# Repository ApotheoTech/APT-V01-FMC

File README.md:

# APT-V01-FMC
CopyRight 2023 ApotheoTech 

## Description

The GPIO board is made mostly for enabling GPIO access to any FMC card connector. It has a Raspberry Pi hat compliant connector, and two PMODs that can be used by PMODs that require two adjacent connectors. 

It also has an M.2 Key E connector with a ULPI USB 2.0 interface and 1 PCIe TX and RX connection to support Wifi and Bluetooth. 

## Example Designs 

Navigate up to the repository under example designs (TBD link). 

## Projected Use Cases

Mostly Debugging and providing Wifi accesses to PetaLinux builds

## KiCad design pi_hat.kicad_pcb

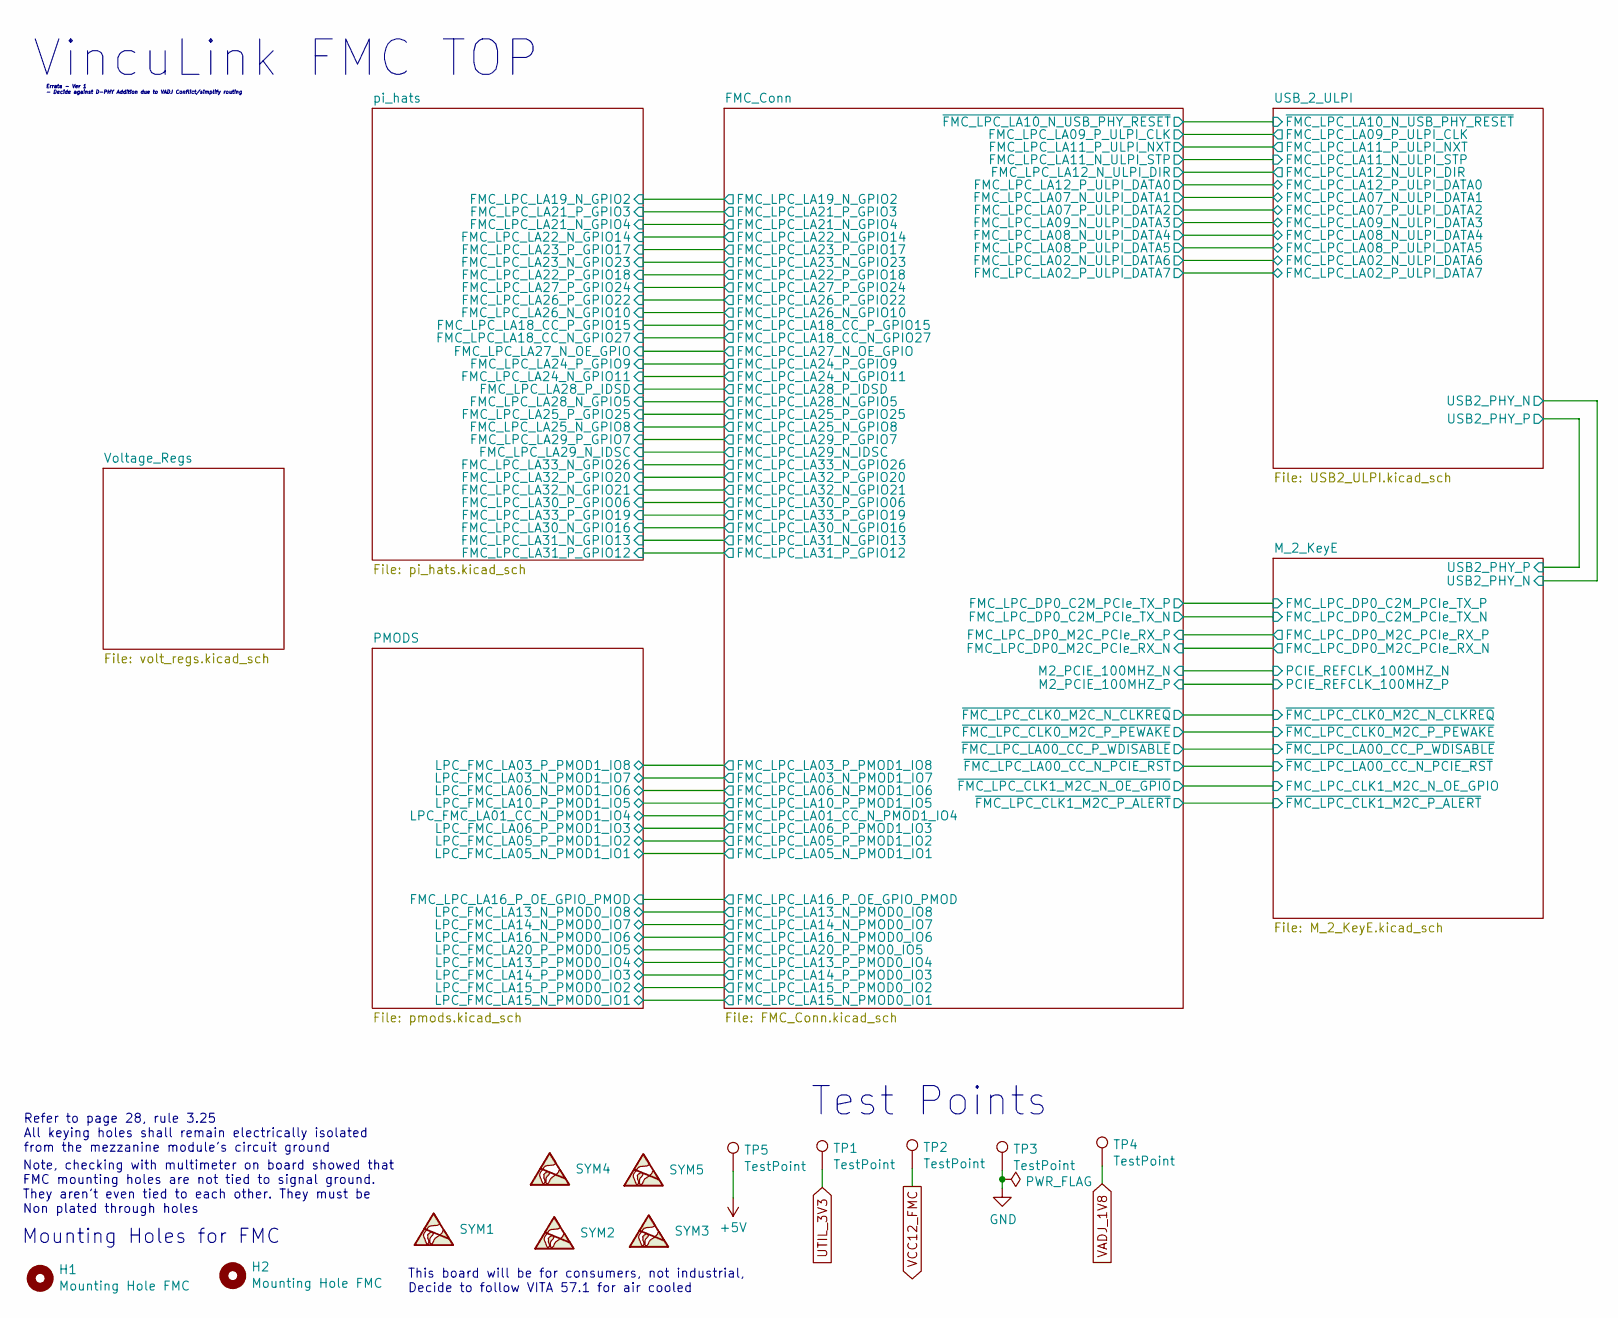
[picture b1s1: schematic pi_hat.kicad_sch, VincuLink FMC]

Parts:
H1, H2: Mounting Hole FMC; MountingHole_2.7mm_M2.5_Pad_2.9mm
SYM1: SYM_ESD_Small; ApotheoTech_Sym
SYM2: SYM_ESD_Small; WEEE-Logo_4.2x6mm_SilkScreen
SYM3: SYM_ESD_Small; ESD-Logo_6.6x6mm_SilkScreen
SYM4: SYM_ESD_Small; CE-Logo_8.5x6mm_SilkScreen
SYM5: SYM_ESD_Small; UKCA_Logo_8_5mm
TP1, TP2, TP3, TP4, TP5: TestPoint

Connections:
+5V: TP5.1; also elsewhere on the board
GND: TP3.1; also elsewhere on the board
UTIL_3V3: TP1.1; also elsewhere on the board
VADJ_1V8: TP4.1; also elsewhere on the board
VCC12_FMC: TP2.1; also elsewhere on the board

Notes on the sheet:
Refer to page 28, rule 3.25 All keying holes shall remain electrically isolated from the mezzanine module's circuit ground
Mounting Holes for FMC
Test Points
Note, checking with multimeter on board showed that FMC mounting holes are not tied to signal ground. They aren't even tied to each other. They must be Non plated through holes
Errata - Ver 1 - Decide against D-PHY Addition due to VADJ Conflict/simplify routing
VincuLink FMC TOP
This board will be for consumers, not industrial, Decide to follow VITA 57.1 for air cooled

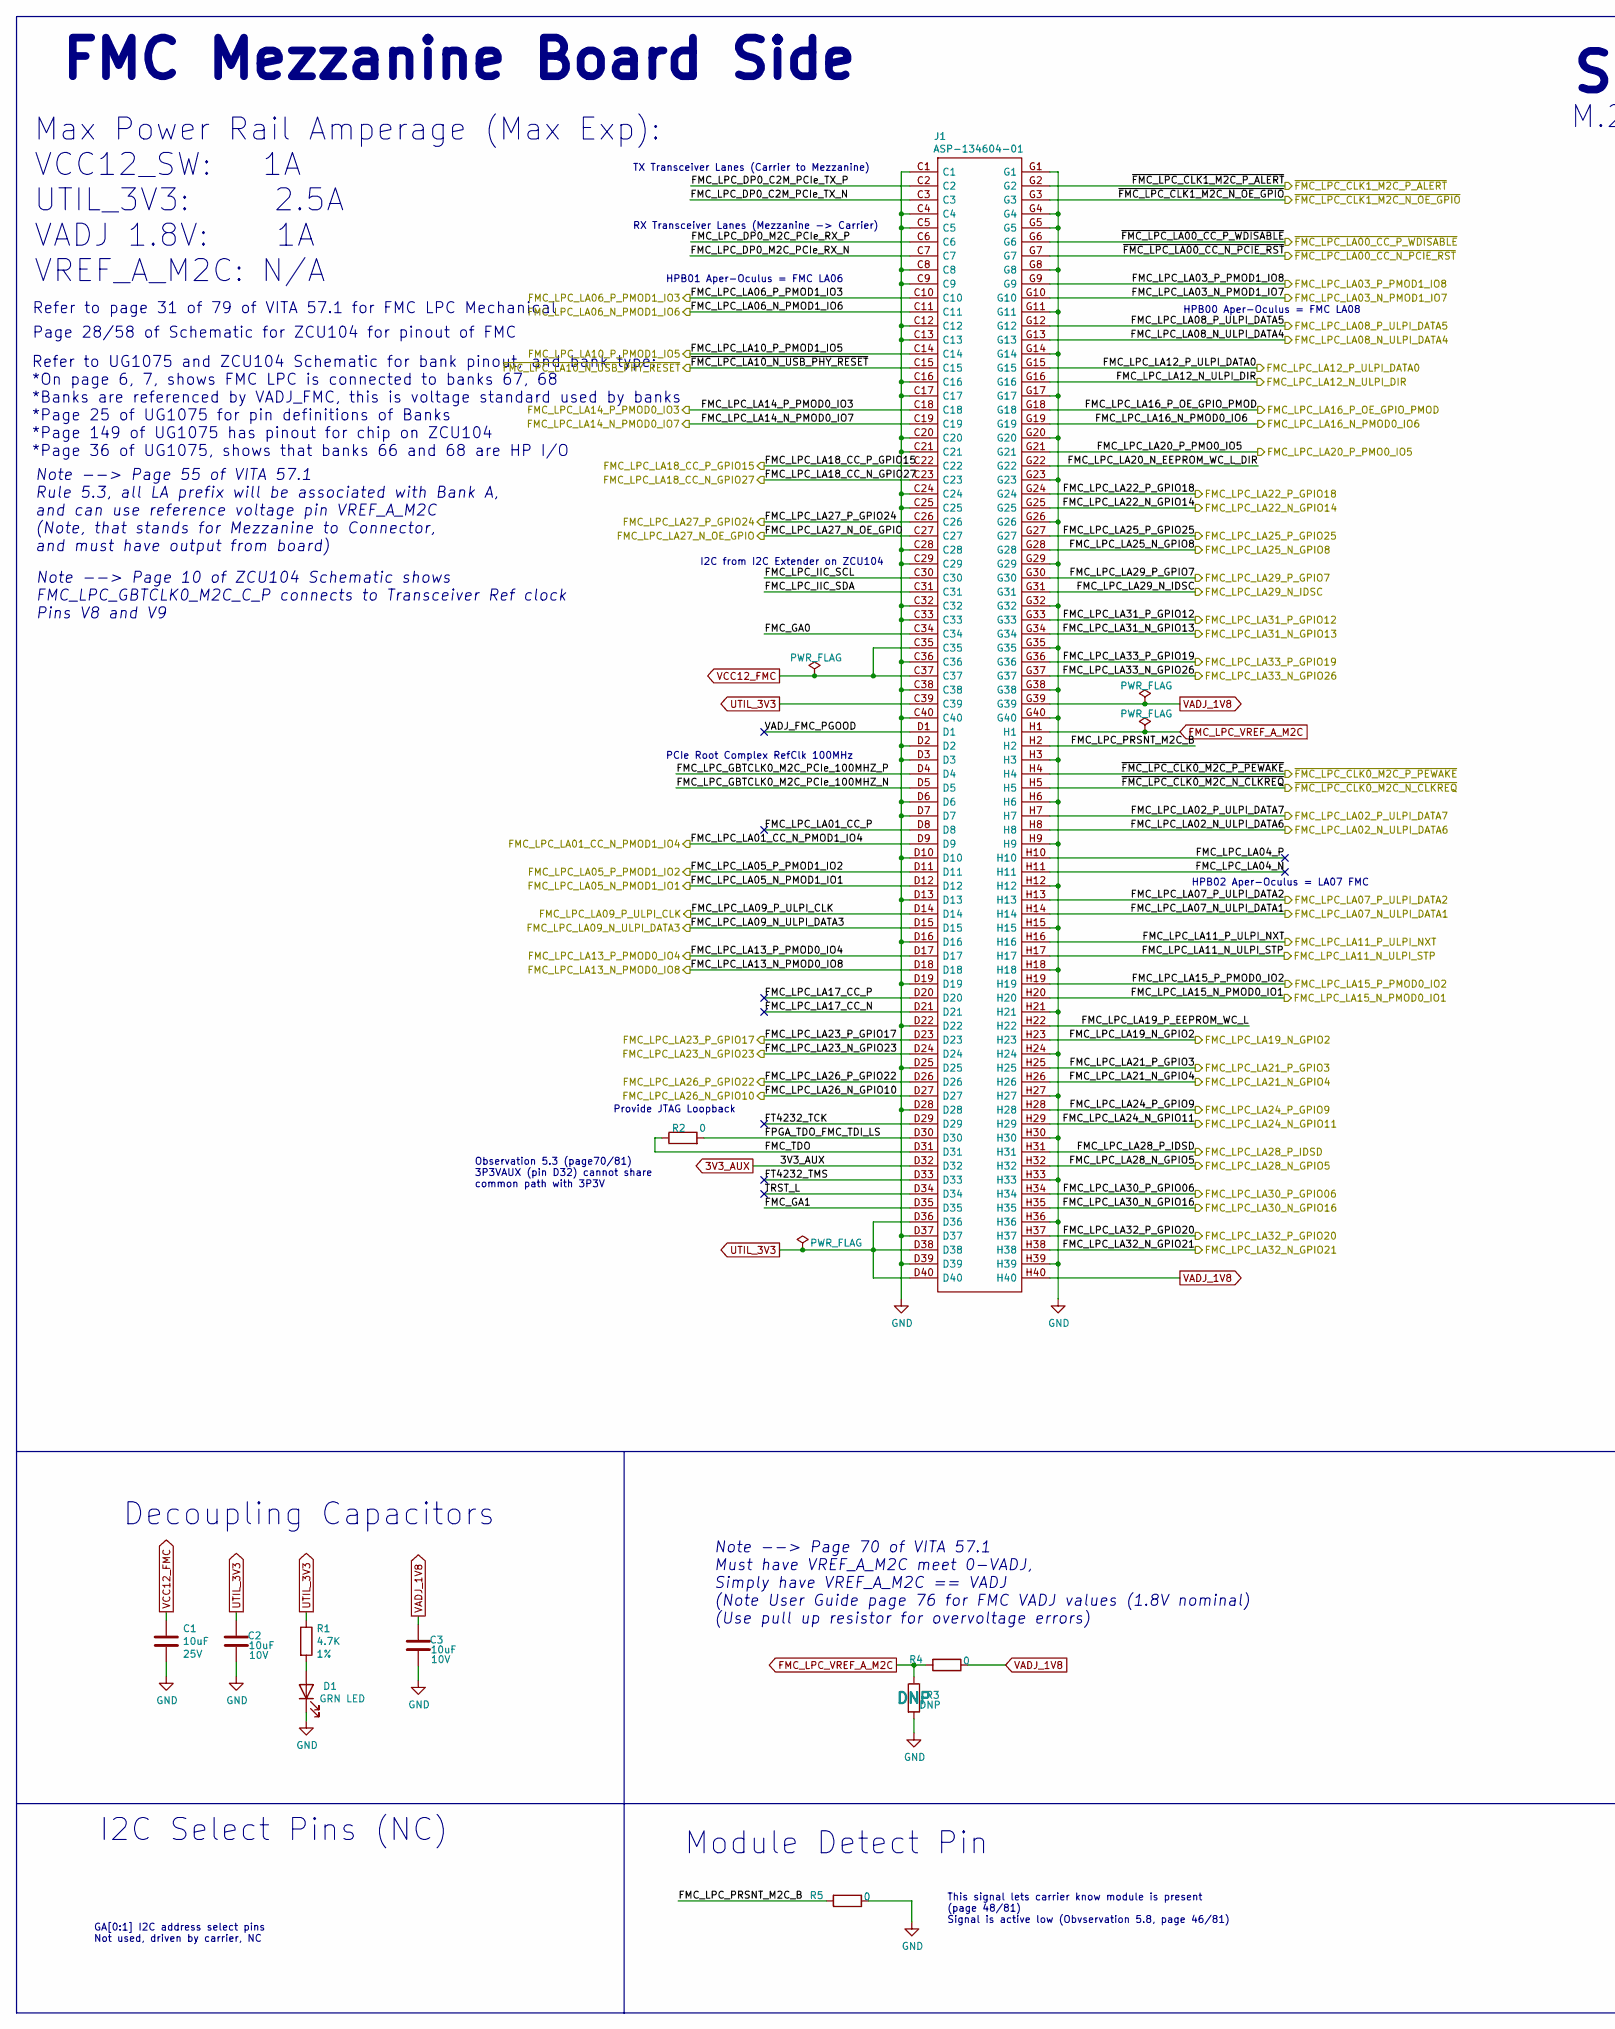
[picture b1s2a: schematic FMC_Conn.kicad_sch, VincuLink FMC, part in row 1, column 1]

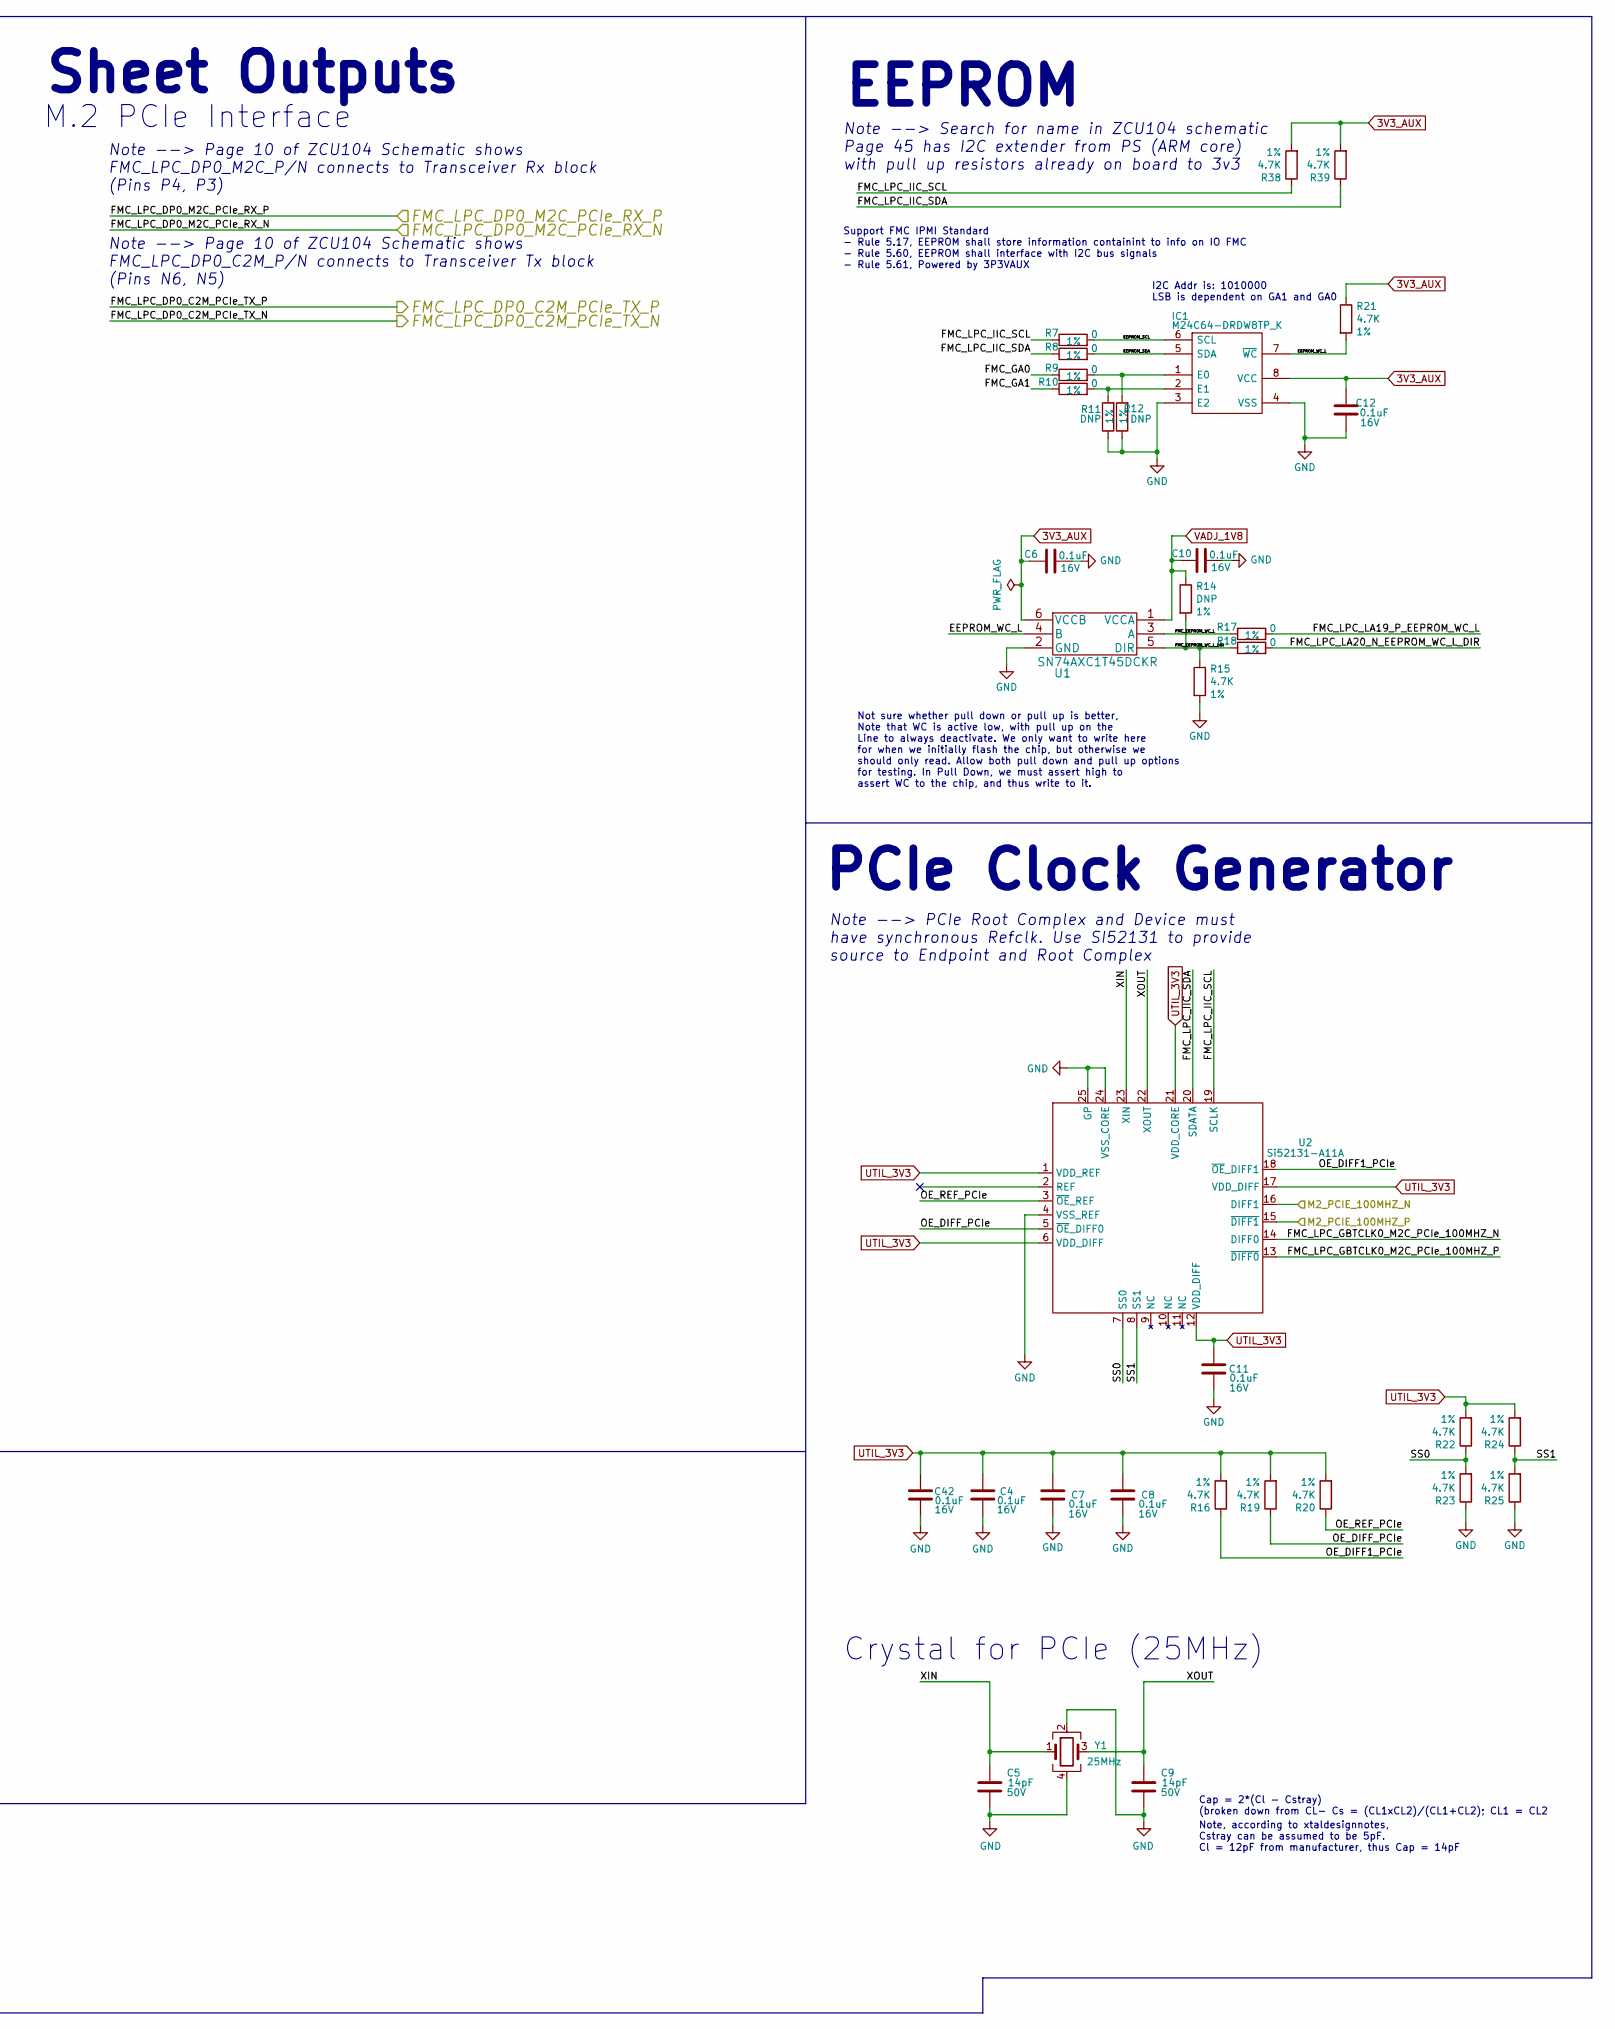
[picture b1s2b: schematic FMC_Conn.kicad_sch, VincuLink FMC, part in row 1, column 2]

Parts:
C1: 10uF; C_0805_2012Metric; Tolerance +-20%; Voltage 25V; PartNumber GRM21BR61E106MA73L
C2, C3: 10uF; C_0603_1608Metric; Tolerance +-10%; Voltage 10V; PartNumber GRM188R61A106KE69D
C4, C6, C7, C8, C10, C11, C12, C42: 0.1uF; C_0402_1005Metric; Tolerance +-10%; Voltage 16V; PartNumber EMK105B7104KV-F
C5, C9: 14pF; C_0402_1005Metric; Voltage 50V; PartNumber 04025U140FAT2A
D1: GRN LED; D_0402_1005Metric; PartNumber 5988A80107F
IC1: M24C64-DRDW8TP_K; Mouser Part Number 511-M24C64-DRDW8TP/K
J1: ASP-134604-01; ASP13460401; Mouser Part Number 200-ASP-134604-01
R1, R15, R16, R19, R20, R21, R22, R23, R24, R25, R38, R39: 4.7K; R_0402_1005Metric; Tolerance 1%; PartNumber CRCW04024K70FKED
R2, R4, R5: 0; R_0402_1005Metric; PartNumber CRCW04020000Z0EDHP
R3: DNP; R_0402_1005Metric; PartNumber CRCW04020000Z0EDHP
R7, R8, R9, R10, R17, R18: 0; R_0402_1005Metric; Tolerance 1%; PartNumber CRCW04020000Z0EDHP
R11, R12: DNP; R_0402_1005Metric; Tolerance 1%; PartNumber CRCW04020000Z0EDHP
R14: DNP; R_0402_1005Metric; Tolerance 1%; PartNumber CRCW04024K70FKED
U1: SN74AXC1T45DCKR
U2: Si52131-A11A; Si52131_QFN-24-1EP_4x4mm_P0.5mm_EP2.7x2.7mm
Y1: 25MHz; Crystal_SMD_3225-4Pin_3.2x2.5mm; PartNumber 830105863709

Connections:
3V3_AUX: C6.1, C12.2, IC1.8 (VCC), J1.D32, R21.1, R38.2, R39.2, U1.6 (VCCB)
/FMC_Conn/EEPROM_SCL: IC1.6 (SCL), R7.2
/FMC_Conn/EEPROM_SDA: IC1.5 (SDA), R8.2
/FMC_Conn/EEPROM_WC_L: IC1.7 (~WC), R21.2, U1.4 (B)
/FMC_Conn/FMC_EEPROM_WC_L: R17.1, U1.3 (A)
/FMC_Conn/FMC_EEPROM_WC_L_DIR: R14.2, R15.1, R18.1, U1.5 (DIR)
/FMC_Conn/FMC_GA0: J1.C34, R9.1
/FMC_Conn/FMC_GA1: J1.D35, R10.1
/FMC_Conn/FMC_LPC_DP0_C2M_PCIe_TX_N: J1.C3; also elsewhere on the board
/FMC_Conn/FMC_LPC_DP0_C2M_PCIe_TX_P: J1.C2; also elsewhere on the board
/FMC_Conn/FMC_LPC_DP0_M2C_PCIe_RX_N: J1.C7; also elsewhere on the board
/FMC_Conn/FMC_LPC_DP0_M2C_PCIe_RX_P: J1.C6; also elsewhere on the board
/FMC_Conn/FMC_LPC_GBTCLK0_M2C_PCIe_100MHZ_N: J1.D5, U2.14 (DIFF0)
/FMC_Conn/FMC_LPC_GBTCLK0_M2C_PCIe_100MHZ_P: J1.D4, U2.13 (~DIFF0)
/FMC_Conn/FMC_LPC_IIC_SCL: J1.C30, R7.1, R38.1, U2.19 (SCLK)
/FMC_Conn/FMC_LPC_IIC_SDA: J1.C31, R8.1, R39.1, U2.20 (SDATA)
/FMC_Conn/FMC_LPC_LA01_CC_N_PMOD1_IO4: J1.D9; also elsewhere on the board
/FMC_Conn/FMC_LPC_LA01_CC_P: J1.D8
/FMC_Conn/FMC_LPC_LA02_N_ULPI_DATA6: J1.H8; also elsewhere on the board
/FMC_Conn/FMC_LPC_LA02_P_ULPI_DATA7: J1.H7; also elsewhere on the board
/FMC_Conn/FMC_LPC_LA03_N_PMOD1_IO7: J1.G10; also elsewhere on the board
/FMC_Conn/FMC_LPC_LA03_P_PMOD1_IO8: J1.G9; also elsewhere on the board
/FMC_Conn/FMC_LPC_LA04_N: J1.H11
/FMC_Conn/FMC_LPC_LA04_P: J1.H10
/FMC_Conn/FMC_LPC_LA05_N_PMOD1_IO1: J1.D12; also elsewhere on the board
/FMC_Conn/FMC_LPC_LA05_P_PMOD1_IO2: J1.D11; also elsewhere on the board
/FMC_Conn/FMC_LPC_LA06_N_PMOD1_IO6: J1.C11; also elsewhere on the board
/FMC_Conn/FMC_LPC_LA06_P_PMOD1_IO3: J1.C10; also elsewhere on the board
/FMC_Conn/FMC_LPC_LA07_N_ULPI_DATA1: J1.H14; also elsewhere on the board
/FMC_Conn/FMC_LPC_LA07_P_ULPI_DATA2: J1.H13; also elsewhere on the board
/FMC_Conn/FMC_LPC_LA08_N_ULPI_DATA4: J1.G13; also elsewhere on the board
/FMC_Conn/FMC_LPC_LA08_P_ULPI_DATA5: J1.G12; also elsewhere on the board
/FMC_Conn/FMC_LPC_LA09_N_ULPI_DATA3: J1.D15; also elsewhere on the board
/FMC_Conn/FMC_LPC_LA09_P_ULPI_CLK: J1.D14; also elsewhere on the board
/FMC_Conn/FMC_LPC_LA10_P_PMOD1_IO5: J1.C14; also elsewhere on the board
/FMC_Conn/FMC_LPC_LA11_N_ULPI_STP: J1.H17; also elsewhere on the board
/FMC_Conn/FMC_LPC_LA11_P_ULPI_NXT: J1.H16; also elsewhere on the board
/FMC_Conn/FMC_LPC_LA12_N_ULPI_DIR: J1.G16; also elsewhere on the board
/FMC_Conn/FMC_LPC_LA12_P_ULPI_DATA0: J1.G15; also elsewhere on the board
/FMC_Conn/FMC_LPC_LA13_N_PMOD0_IO8: J1.D18; also elsewhere on the board
/FMC_Conn/FMC_LPC_LA13_P_PMOD0_IO4: J1.D17; also elsewhere on the board
/FMC_Conn/FMC_LPC_LA14_N_PMOD0_IO7: J1.C19; also elsewhere on the board
/FMC_Conn/FMC_LPC_LA14_P_PMOD0_IO3: J1.C18; also elsewhere on the board
/FMC_Conn/FMC_LPC_LA15_N_PMOD0_IO1: J1.H20; also elsewhere on the board
/FMC_Conn/FMC_LPC_LA15_P_PMOD0_IO2: J1.H19; also elsewhere on the board
/FMC_Conn/FMC_LPC_LA16_N_PMOD0_IO6: J1.G19; also elsewhere on the board
/FMC_Conn/FMC_LPC_LA16_P_OE_GPIO_PMOD: J1.G18; also elsewhere on the board
/FMC_Conn/FMC_LPC_LA17_CC_N: J1.D21
/FMC_Conn/FMC_LPC_LA17_CC_P: J1.D20
/FMC_Conn/FMC_LPC_LA18_CC_N_GPIO27: J1.C23; also elsewhere on the board
/FMC_Conn/FMC_LPC_LA18_CC_P_GPIO15: J1.C22; also elsewhere on the board
/FMC_Conn/FMC_LPC_LA19_N_GPIO2: J1.H23; also elsewhere on the board
/FMC_Conn/FMC_LPC_LA19_P_EEPROM_WC_L: J1.H22, R17.2
/FMC_Conn/FMC_LPC_LA20_N_EEPROM_WC_L_DIR: J1.G22, R18.2
/FMC_Conn/FMC_LPC_LA20_P_PMO0_IO5: J1.G21; also elsewhere on the board
/FMC_Conn/FMC_LPC_LA21_N_GPIO4: J1.H26; also elsewhere on the board
/FMC_Conn/FMC_LPC_LA21_P_GPIO3: J1.H25; also elsewhere on the board
/FMC_Conn/FMC_LPC_LA22_N_GPIO14: J1.G25; also elsewhere on the board
/FMC_Conn/FMC_LPC_LA22_P_GPIO18: J1.G24; also elsewhere on the board
/FMC_Conn/FMC_LPC_LA23_N_GPIO23: J1.D24; also elsewhere on the board
/FMC_Conn/FMC_LPC_LA23_P_GPIO17: J1.D23; also elsewhere on the board
/FMC_Conn/FMC_LPC_LA24_N_GPIO11: J1.H29; also elsewhere on the board
/FMC_Conn/FMC_LPC_LA24_P_GPIO9: J1.H28; also elsewhere on the board
/FMC_Conn/FMC_LPC_LA25_N_GPIO8: J1.G28; also elsewhere on the board
/FMC_Conn/FMC_LPC_LA25_P_GPIO25: J1.G27; also elsewhere on the board
/FMC_Conn/FMC_LPC_LA26_N_GPIO10: J1.D27; also elsewhere on the board
/FMC_Conn/FMC_LPC_LA26_P_GPIO22: J1.D26; also elsewhere on the board
/FMC_Conn/FMC_LPC_LA27_P_GPIO24: J1.C26; also elsewhere on the board
/FMC_Conn/FMC_LPC_LA28_N_GPIO5: J1.H32; also elsewhere on the board
/FMC_Conn/FMC_LPC_LA28_P_IDSD: J1.H31; also elsewhere on the board
/FMC_Conn/FMC_LPC_LA29_N_IDSC: J1.G31; also elsewhere on the board
/FMC_Conn/FMC_LPC_LA29_P_GPIO7: J1.G30; also elsewhere on the board
/FMC_Conn/FMC_LPC_LA30_N_GPIO16: J1.H35; also elsewhere on the board
/FMC_Conn/FMC_LPC_LA30_P_GPIO06: J1.H34; also elsewhere on the board
/FMC_Conn/FMC_LPC_LA31_N_GPIO13: J1.G34; also elsewhere on the board
/FMC_Conn/FMC_LPC_LA31_P_GPIO12: J1.G33; also elsewhere on the board
/FMC_Conn/FMC_LPC_LA32_N_GPIO21: J1.H38; also elsewhere on the board
/FMC_Conn/FMC_LPC_LA32_P_GPIO20: J1.H37; also elsewhere on the board
/FMC_Conn/FMC_LPC_LA33_N_GPIO26: J1.G37; also elsewhere on the board
/FMC_Conn/FMC_LPC_LA33_P_GPIO19: J1.G36; also elsewhere on the board
/FMC_Conn/FMC_LPC_PRSNT_M2C_B: J1.H2, R5.2
/FMC_Conn/FMC_TDO: J1.D31, R2.1
/FMC_Conn/FPGA_TDO_FMC_TDI_LS: J1.D30, R2.2
/FMC_Conn/FT4232_TCK: J1.D29
/FMC_Conn/FT4232_TMS: J1.D33
/FMC_Conn/M2_PCIE_100MHZ_N: U2.16 (DIFF1); also elsewhere on the board
/FMC_Conn/M2_PCIE_100MHZ_P: U2.15 (~DIFF1); also elsewhere on the board
/FMC_Conn/OE_DIFF1_PCIe: R16.1, U2.18 (~OE_DIFF1)
/FMC_Conn/OE_DIFF_PCIe: R19.1, U2.5 (~OE_DIFF0)
/FMC_Conn/OE_REF_PCIe: R20.1, U2.3 (~OE_REF)
/FMC_Conn/SS0: R22.1, R23.2, U2.7 (SS0)
/FMC_Conn/SS1: R24.1, R25.2, U2.8 (SS1)
/FMC_Conn/TRST_L: J1.D34
/FMC_Conn/VADJ_FMC_PGOOD: J1.D1
/FMC_Conn/XIN: C5.2, U2.23 (XIN), Y1.1
/FMC_Conn/XOUT: C9.2, U2.22 (XOUT), Y1.3
/FMC_Conn/~FMC_LPC_CLK0_M2C_N_CLKREQ: J1.H5; also elsewhere on the board
/FMC_Conn/~FMC_LPC_CLK0_M2C_P_PEWAKE: J1.H4; also elsewhere on the board
/FMC_Conn/~FMC_LPC_CLK1_M2C_P_ALERT: J1.G2; also elsewhere on the board
/FMC_Conn/~FMC_LPC_LA00_CC_N_PCIE_RST: J1.G7; also elsewhere on the board
/FMC_Conn/~FMC_LPC_LA00_CC_P_WDISABLE: J1.G6; also elsewhere on the board
/FMC_Conn/~FMC_LPC_LA10_N_USB_PHY_RESET: J1.C15; also elsewhere on the board
FMC_LPC_VREF_A_M2C: J1.H1, R3.1, R4.2
GND: C1.2, C2.1, C3.1, C4.2, C5.1, C6.2, C7.2, C8.2, C9.1, C10.2, C11.2, C12.1, C42.2, D1.1 (K), IC1.3 (E2), IC1.4 (VSS), J1.C1, J1.C4, J1.C5, J1.C8, J1.C9, J1.C12, J1.C13, J1.C16, J1.C17, J1.C20, J1.C21, J1.C24, J1.C25, J1.C28, J1.C29, J1.C32, J1.C33, J1.C36, J1.C38, J1.C40, J1.D2, J1.D3, J1.D6, J1.D7, J1.D10, J1.D13, J1.D16, J1.D19, J1.D22, J1.D25, J1.D28, J1.D37, J1.D39, J1.G1, J1.G4, J1.G5, J1.G8, J1.G11, J1.G14, J1.G17, J1.G20, J1.G23, J1.G26, J1.G29, J1.G32, J1.G35, J1.G38, J1.G40, J1.H3, J1.H6, J1.H9, J1.H12, J1.H15, J1.H18, J1.H21, J1.H24, J1.H27, J1.H30, J1.H33, J1.H36, J1.H39, R3.2, R5.1, R11.1, R12.1, R15.2, R23.1, R25.1, U1.2 (GND), U2.4 (VSS_REF), U2.24 (VSS_CORE), U2.25 (GP), Y1.2, Y1.4; also elsewhere on the board
unnamed: D1.2 (A), R1.2
unnamed: IC1.1 (E0), R9.2, R12.2
unnamed: IC1.2 (E1), R10.2, R11.2
UTIL_3V3: C2.2, C4.1, C7.1, C8.1, C11.1, C42.1, J1.C39, J1.D36, J1.D38, J1.D40, R1.1, R16.2, R19.2, R20.2, R22.2, R24.2, U2.1 (VDD_REF), U2.6 (VDD_DIFF), U2.12 (VDD_DIFF), U2.17 (VDD_DIFF), U2.21 (VDD_CORE); also elsewhere on the board
VADJ_1V8: C3.2, C10.1, J1.G39, J1.H40, R4.1, R14.1, U1.1 (VCCA); also elsewhere on the board
VCC12_FMC: C1.1, J1.C35, J1.C37; also elsewhere on the board

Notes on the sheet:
M.2 PCIe Interface
Note --> Page 10 of ZCU104 Schematic shows FMC_LPC_DP0_M2C_P/N connects to Transceiver Rx block (Pins P4, P3)
Crystal for PCIe (25MHz)
I2C Select Pins (NC)
Module Detect Pin
Note --> Page 10 of ZCU104 Schematic shows FMC_LPC_GBTCLK0_M2C_C_P connects to Transceiver Ref clock Pins V8 and V9
Note --> PCIe Root Complex and Device must have synchronous Refclk. Use SI52131 to provide source to Endpoint and Root Complex
Note, according to xtaldesignnotes, Cstray can be assumed to be 5pF. Cl = 12pF from manufacturer, thus Cap = 14pF
EEPROM
Refer to UG1075 and ZCU104 Schematic for bank pinout, and bank type: *On page 6, 7, shows FMC LPC is connected to banks 67, 68 *Banks are referenced by VADJ_FMC, this is voltage standard used by banks *Page 25 of UG1075 for pin definitions of Banks *Page 149 of UG1075 has pinout for chip on ZCU104 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
GA[0:1] I2C address select pins Not used, driven by carrier, NC
Note --> Page 70 of VITA 57.1 Must have VREF_A_M2C meet 0-VADJ, Simply have VREF_A_M2C == VADJ (Note User Guide page 76 for FMC VADJ values (1.8V nominal) (Use pull up resistor for overvoltage errors)
Support FMC IPMI Standard - Rule 5.17, EEPROM shall store information containint to info on IO FMC - Rule 5.60, EEPROM shall interface with I2C bus signals - Rule 5.61, Powered by 3P3VAUX
Note --> Page 55 of VITA 57.1 Rule 5.3, all LA prefix will be associated with Bank A, and can use reference voltage pin VREF_A_M2C (Note, that stands for Mezzanine to Connector, and must have output from board)
PCIe Root Complex RefClk 100MHz
Page 28/58 of Schematic for ZCU104 for pinout of FMC
Sheet Outputs
FMC Mezzanine Board Side
This signal lets carrier know module is present (page 48/81) Signal is active low (Obvservation 5.8, page 46/81)
Provide JTAG Loopback
Note --> Search for name in ZCU104 schematic Page 45 has I2C extender from PS (ARM core) with pull up resistors already on board to 3v3
I2C Addr is: 1010000 LSB is dependent on GA1 and GA0
HPB01 Aper-Oculus = FMC LA06
PCIe Clock Generator
I2C from I2C Extender on ZCU104
Refer to page 31 of 79 of VITA 57.1 for FMC LPC Mechanical
Cap = 2*(Cl - Cstray) (broken down from CL- Cs = (CL1xCL2)/(CL1+CL2); CL1 = CL2
Not sure whether pull down or pull up is better, Note that WC is active low, with pull up on the Line to always deactivate. We only want to write here for when we initially flash the chip, but otherwise we should only read. Allow both pull down and pull up options for testing. In Pull Down, we must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
Max Power Rail Amperage (Max Exp): VCC12_SW: 1A UTIL_3V3: 2.5A VADJ 1.8V: 1A VREF_A_M2C: N/A
RX Transceiver Lanes (Mezzanine -> Carrier)
Decoupling Capacitors
HPB00 Aper-Oculus = FMC LA08
HPB02 Aper-Oculus = LA07 FMC
Observation 5.3 (page70/81) 3P3VAUX (pin D32) cannot share common path with 3P3V
Note --> Page 10 of ZCU104 Schematic shows FMC_LPC_DP0_C2M_P/N connects to Transceiver Tx block (Pins N6, N5)
TX Transceiver Lanes (Carrier to Mezzanine)

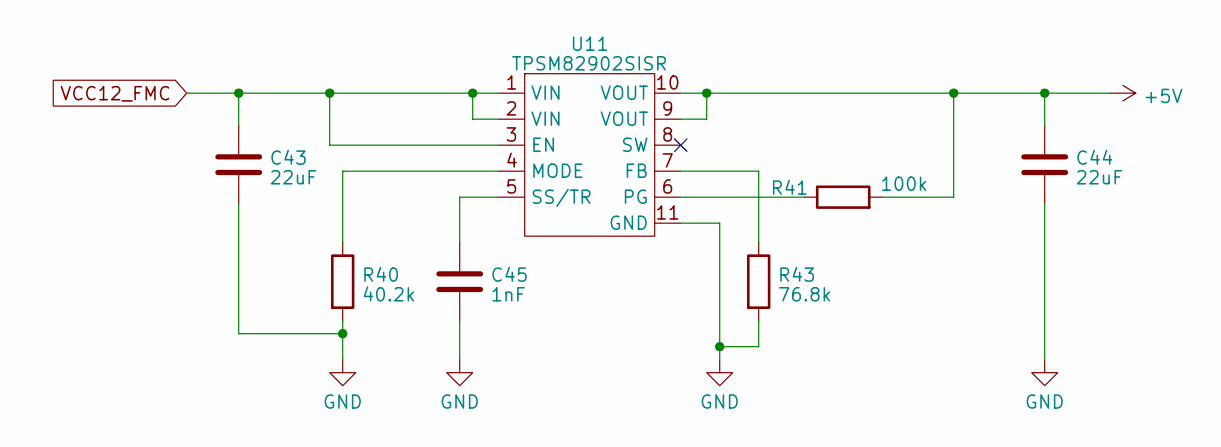
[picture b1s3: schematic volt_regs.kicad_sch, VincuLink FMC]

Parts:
C43, C44: 22uF; C_0805_2012Metric; Voltage 35V; PartNumber C2012X5R1V226M125AC
C45: 1nF; C_0402_1005Metric; Voltage 10V; Tolerance +-10%; PartNumber GRM155R61A102KA01D
R40: 40.2k; R_0402_1005Metric; PartNumber ERJ-2RKF4022X
R41: 100k; R_0402_1005Metric; PartNumber CRCW0402100KFKEDHP
R43: 76.8k; R_0402_1005Metric; PartNumber CRCW040276K8FKED
U11: TPSM82902SISR

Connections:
+5V: C44.1, R41.2, U11.9 (VOUT), U11.10 (VOUT); also elsewhere on the board
GND: C43.2, C44.2, C45.2, R40.2, R43.2, U11.11 (GND); also elsewhere on the board
unnamed: R43.1, U11.7 (FB)
unnamed: R40.1, U11.4 (MODE)
unnamed: R41.1, U11.6 (PG)
unnamed: C45.1, U11.5 (SS/TR)
VCC12_FMC: C43.1, U11.1 (VIN), U11.2 (VIN), U11.3 (EN); also elsewhere on the board

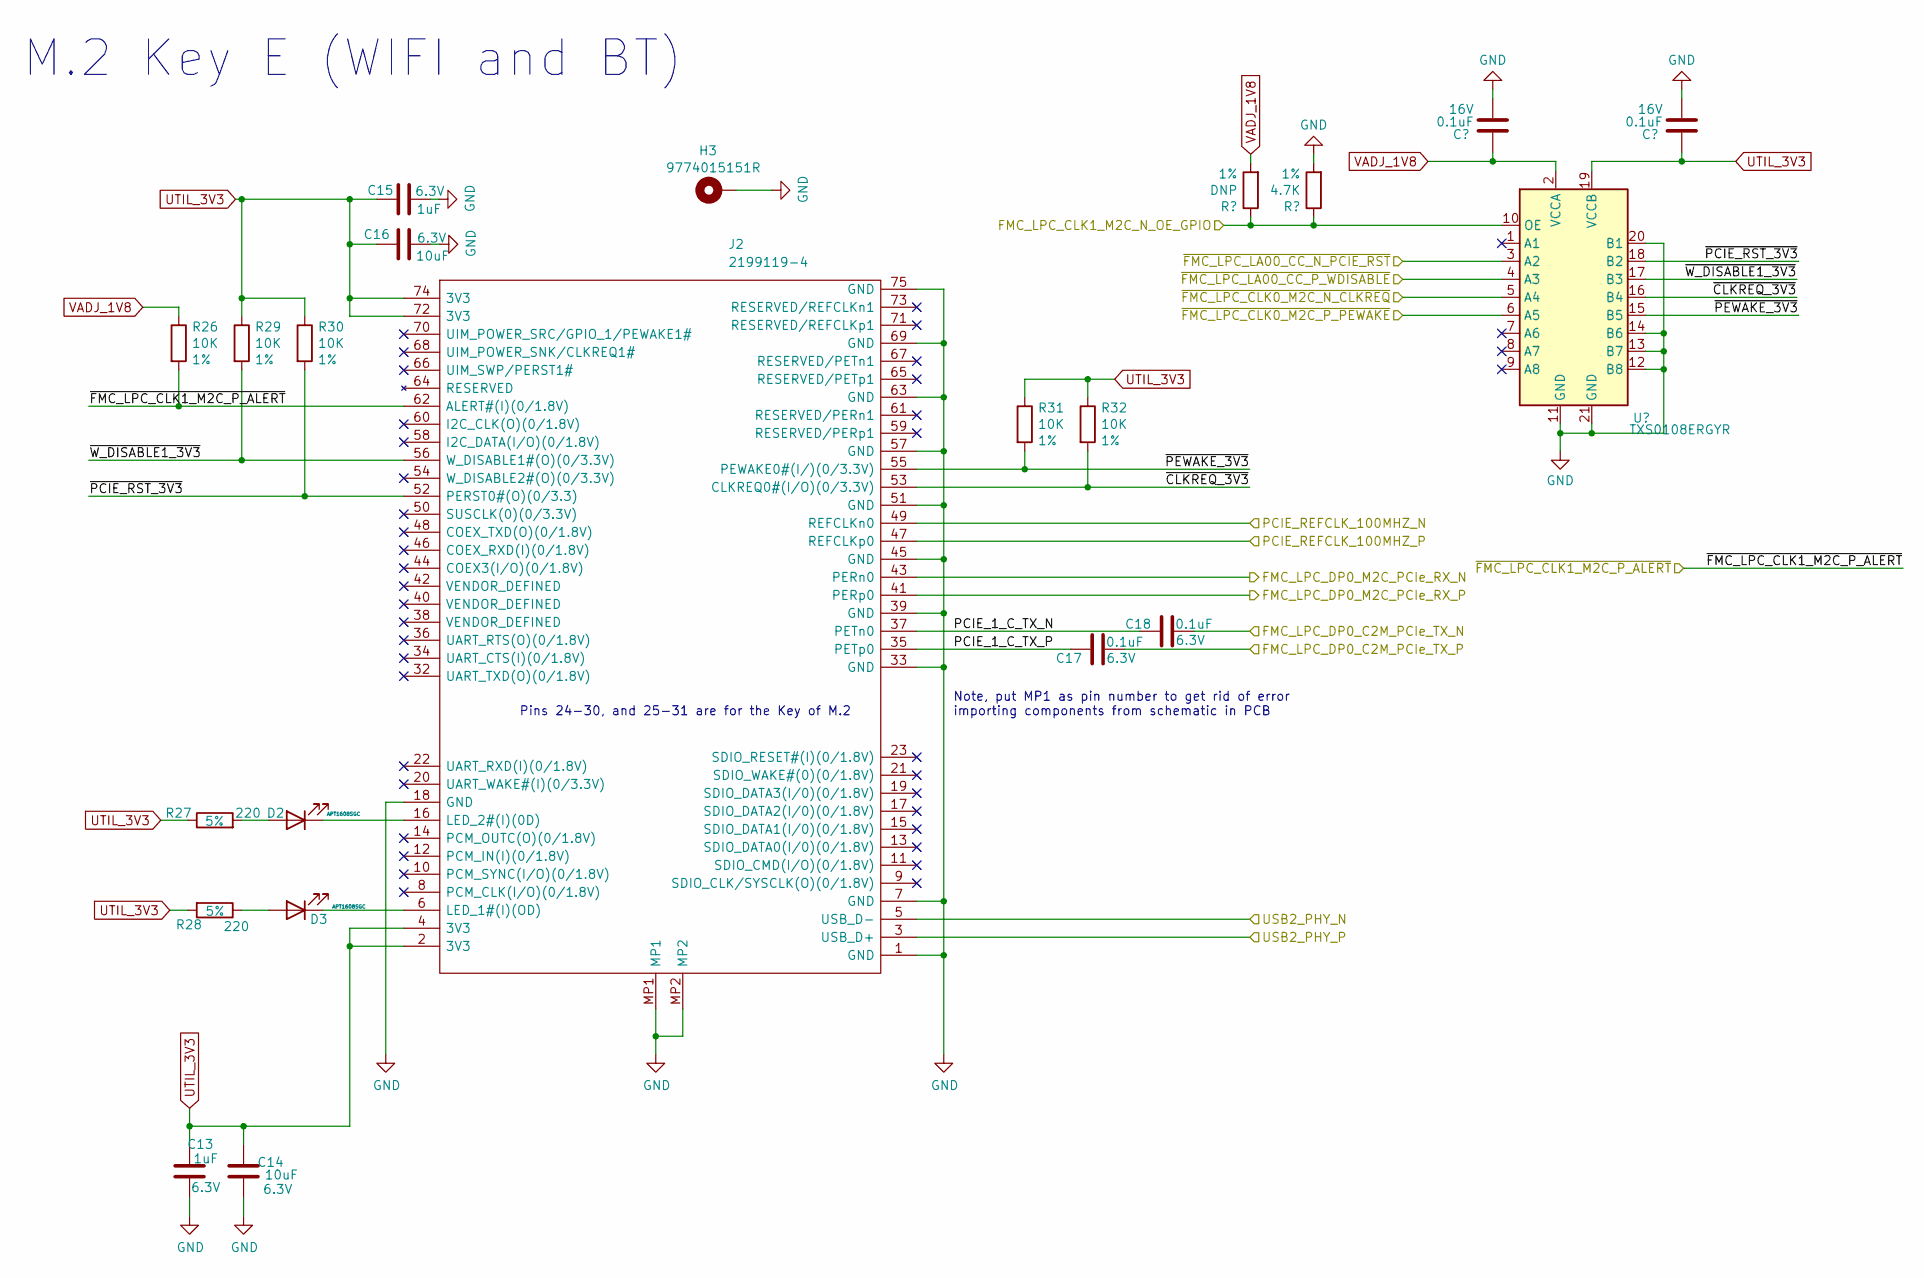
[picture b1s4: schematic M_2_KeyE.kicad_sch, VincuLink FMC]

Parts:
C13, C15: 1uF; C_0402_1005Metric; Voltage 6.3V; PartNumber C0402C105Z9VACTU
C14, C16: 10uF; C_0603_1608Metric; Voltage 6.3V; PartNumber 06036D106MAT2A
C17, C18: 0.1uF; C_0402_1005Metric; Voltage 6.3V; PartNumber C1005X5R0J104K050BA
C19, C20: 0.1uF; C_0402_1005Metric; Tolerance +-10%; Voltage 16V; PartNumber EMK105B7104KV-F
D2, D3: APT1608SGC; LED_0603_1608Metric
H3: 9774015151R
J2: 2199119-4; Mouser Part Number 571-2199119-4
R26, R29, R30, R31, R32: 10K; R_0402_1005Metric; Tolerance 1%; PartNumber ERJ-2RKF1002X
R27, R28: 220; R_0402_1005Metric; PartNumber RC0402JR-07220RL
R36: DNP; R_0402_1005Metric; Tolerance 1%; PartNumber CRCW04024K70FKED
R37: 4.7K; R_0402_1005Metric; Tolerance 1%; PartNumber CRCW04024K70FKED
U3: TXS0108ERGYR; TI_VQFN_RGY0020A

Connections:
/FMC_Conn/FMC_LPC_DP0_C2M_PCIe_TX_N: C18.2; also elsewhere on the board
/FMC_Conn/FMC_LPC_DP0_C2M_PCIe_TX_P: C17.2; also elsewhere on the board
/FMC_Conn/FMC_LPC_DP0_M2C_PCIe_RX_N: J2.43 (PERn0); also elsewhere on the board
/FMC_Conn/FMC_LPC_DP0_M2C_PCIe_RX_P: J2.41 (PERp0); also elsewhere on the board
/FMC_Conn/M2_PCIE_100MHZ_N: J2.49 (REFCLKn0); also elsewhere on the board
/FMC_Conn/M2_PCIE_100MHZ_P: J2.47 (REFCLKp0); also elsewhere on the board
/FMC_Conn/~FMC_LPC_CLK0_M2C_N_CLKREQ: U3.5 (A4); also elsewhere on the board
/FMC_Conn/~FMC_LPC_CLK0_M2C_P_PEWAKE: U3.6 (A5); also elsewhere on the board
/FMC_Conn/~FMC_LPC_CLK1_M2C_P_ALERT: J2.62 (ALERT#(I)(0/1.8V)), R26.2; also elsewhere on the board
/FMC_Conn/~FMC_LPC_LA00_CC_N_PCIE_RST: U3.3 (A2); also elsewhere on the board
/FMC_Conn/~FMC_LPC_LA00_CC_P_WDISABLE: U3.4 (A3); also elsewhere on the board
/M_2_KeyE/PCIE_1_C_TX_N: C18.1, J2.37 (PETn0)
/M_2_KeyE/PCIE_1_C_TX_P: C17.1, J2.35 (PETp0)
/M_2_KeyE/USB2_PHY_N: J2.5 (USB_D-); also elsewhere on the board
/M_2_KeyE/USB2_PHY_P: J2.3 (USB_D+); also elsewhere on the board
/M_2_KeyE/~CLKREQ_3V3: J2.53 (CLKREQ0#(I/O)(0/3.3V)), R32.2, U3.16 (B4)
/M_2_KeyE/~PCIE_RST_3V3: J2.52 (PERST0#(O)(0/3.3)), R30.2, U3.18 (B2)
/M_2_KeyE/~PEWAKE_3V3: J2.55 (PEWAKE0#(I/)(0/3.3V)), R31.2, U3.15 (B5)
/M_2_KeyE/~W_DISABLE1_3V3: J2.56 (W_DISABLE1#(O)(0/3.3V)), R29.2, U3.17 (B3)
GND: C13.1, C14.1, C15.2, C16.2, C19.1, C20.1, H3.1, J2.1 (GND), J2.7 (GND), J2.18 (GND), J2.33 (GND), J2.39 (GND), J2.45 (GND), J2.51 (GND), J2.57 (GND), J2.63 (GND), J2.69 (GND), J2.75 (GND), J2.MP1, J2.MP2, R37.2, U3.11 (GND), U3.12 (B8), U3.13 (B7), U3.14 (B6), U3.20 (B1), U3.21 (GND); also elsewhere on the board
unnamed: D2.2 (A), R27.2
unnamed: D2.1 (K), J2.16 (LED_2#(I)(0D))
unnamed: D3.2 (A), R28.1
unnamed: D3.1 (K), J2.6 (LED_1#(I)(OD))
UTIL_3V3: C13.2, C14.2, C15.1, C16.1, C20.2, J2.2 (3V3), J2.4 (3V3), J2.72 (3V3), J2.74 (3V3), R27.1, R28.2, R29.1, R30.1, R31.1, R32.1, U3.19 (VCCB); also elsewhere on the board
VADJ_1V8: C19.2, R26.1, R36.2, U3.2 (VCCA); also elsewhere on the board

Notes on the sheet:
Pins 24-30, and 25-31 are for the Key of M.2
M.2 Key E (WIFI and BT)
Note, put MP1 as pin number to get rid of error importing components from schematic in PCB
